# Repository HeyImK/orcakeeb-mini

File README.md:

# orcakeeb-mini

A 16-key mechanical macropad featuring a rotary encoder, per-key RGB, and a 0.91-inch OLED screen. The board is built around the Waveshare RP2040-Zero module, which handles the USB-C connection and logic, allowing for a highly compact PCB design. Fully compatible with QMK and KMK (CircuitPython) firmware.

## Pictures

| Top View | Bottom View |
| :---: | :---: |
| /topbrd.png>) | /btmbrd.png>) |

## Features

* **Main Controller:** Waveshare RP2040-Zero, providing a dual-core ARM Cortex-M0+ and natively handling USB-C and 3.3V regulation.
* **Switch Matrix:** 4x4 grid supporting 16 TTC low-profile mechanical switches, fully diode-isolated to prevent ghosting.
* **RGB Leds:** 16 reverse-mounted SK6812MINI-E LEDs sitting flush inside the switch cutouts. Powered directly via the 5V VBUS line.
* **Rotary Encoder:** Standard rotary encoder with push-button functionality. Relies on internal RP2040 pull-up resistors and software debouncing.
* **OLED Display:** I2C header for a standard 0.91" SSD1306 OLED module to display active layers, WPM, or custom graphics.

## Components Used

* **Microcontroller:** Waveshare RP2040-Zero Dev-Board
* **Switches:** 16x Cherry MX Switches or similar knock-offs
* **Diodes:** 16x 1N4148 
* **LEDs:** 16x SK6812MINI-E
* **Screen:** 0.91" SSD1306 I2C OLED Module
* **Miscellaneous:** 1x 10µF Ceramic Cap (for main 5V), 16x 0.1µF Caps (LED decoupling), EC11 (or similar knockoffs) Rotary Encoder

## Bill of Materials (BOM)

| Qty | Component | Footprint | Designator(s) |
| :---: | :--- | :--- | :--- |
| 15 | 100nf Capacitor | C_0603_1608Metric | C1, C2, C3, C5, C6, C7, C8, C9, C10, C11, C12, C13, C14, C15, C16 |
| 1 | 10uf Capacitor | C_0603_1608Metric | C17 |
| 1 | 10nF Capacitor | C_0603_1608Metric | C22 |
| 15 | SK6812MINI-E LED | LED_SK6812MINI-E_3.2x2.8mm_P1.5mm_ReverseMount | D1, D2, D3, D5, D6, D7, D8, D9, D10, D11, D12, D13, D14, D15, D16 |
| 15 | 1N4148W Diode | D_SOD-123 | D17, D18, D19, D20, D21, D22, D23, D24, D25, D26, D27, D28, D30, D31, D32 |
| 2 | 10k Resistor | R_0603_1608Metric | R3, R4 |
| 15 | SW_Push (Cherry MX) | SW_Cherry_MX_1.00u_PCB | SW1, SW2, SW3, SW4, SW5, SW6, SW7, SW8, SW9, SW10, SW11, SW12, SW14, SW15, SW16 |
| 1 | RotaryEncoder_Switch | RotaryEncoder_Alps_EC11E-Switch_Vertical_H20mm | SW19 |
| 1 | RP2040_MICRO | RP2040 MINI | U1 |
| 1 | 0.91_OLED | Untitled | U2 |

| Schematic Design |
| :---: |
| /schematics_orcakeeb.png>) |

| PCB Top Layer Routing | PCB Bottom Layer Routing |
| :---: | :---: |
| /routing_topbrd.png>) | /routing_btmbrd.png>) |

### Connections
* **VBUS (5V):** Routes power straight from the USB-C port to the main 10µF bulk capacitor, then daisy-chains to the VDD pins of all 16 LEDs. 
* **OLED Header:** Connecetd to pins (SDA) G10 (SCK) G9
* **Encoder:** Connected to Pin G4, and A And B pins to G3 and G2
* **RGB Led Data:** Data IN pins connected to G14
  
## License

This hardware project is open-source and licensed under the CERN Open Hardware Licence Version 2 - Strongly Reciprocal (CERN-OHL-S-2.0). 

You are free to copy, modify, distribute, and manufacture this board for personal or commercial use. However, if you modify these schematic or layout files and distribute your new design, you must release those modifications under this exact same CERN-OHL-S-2.0 license.

This design is shared without any warranty or implied guarantee. Check the LICENSE file for the full legal text.

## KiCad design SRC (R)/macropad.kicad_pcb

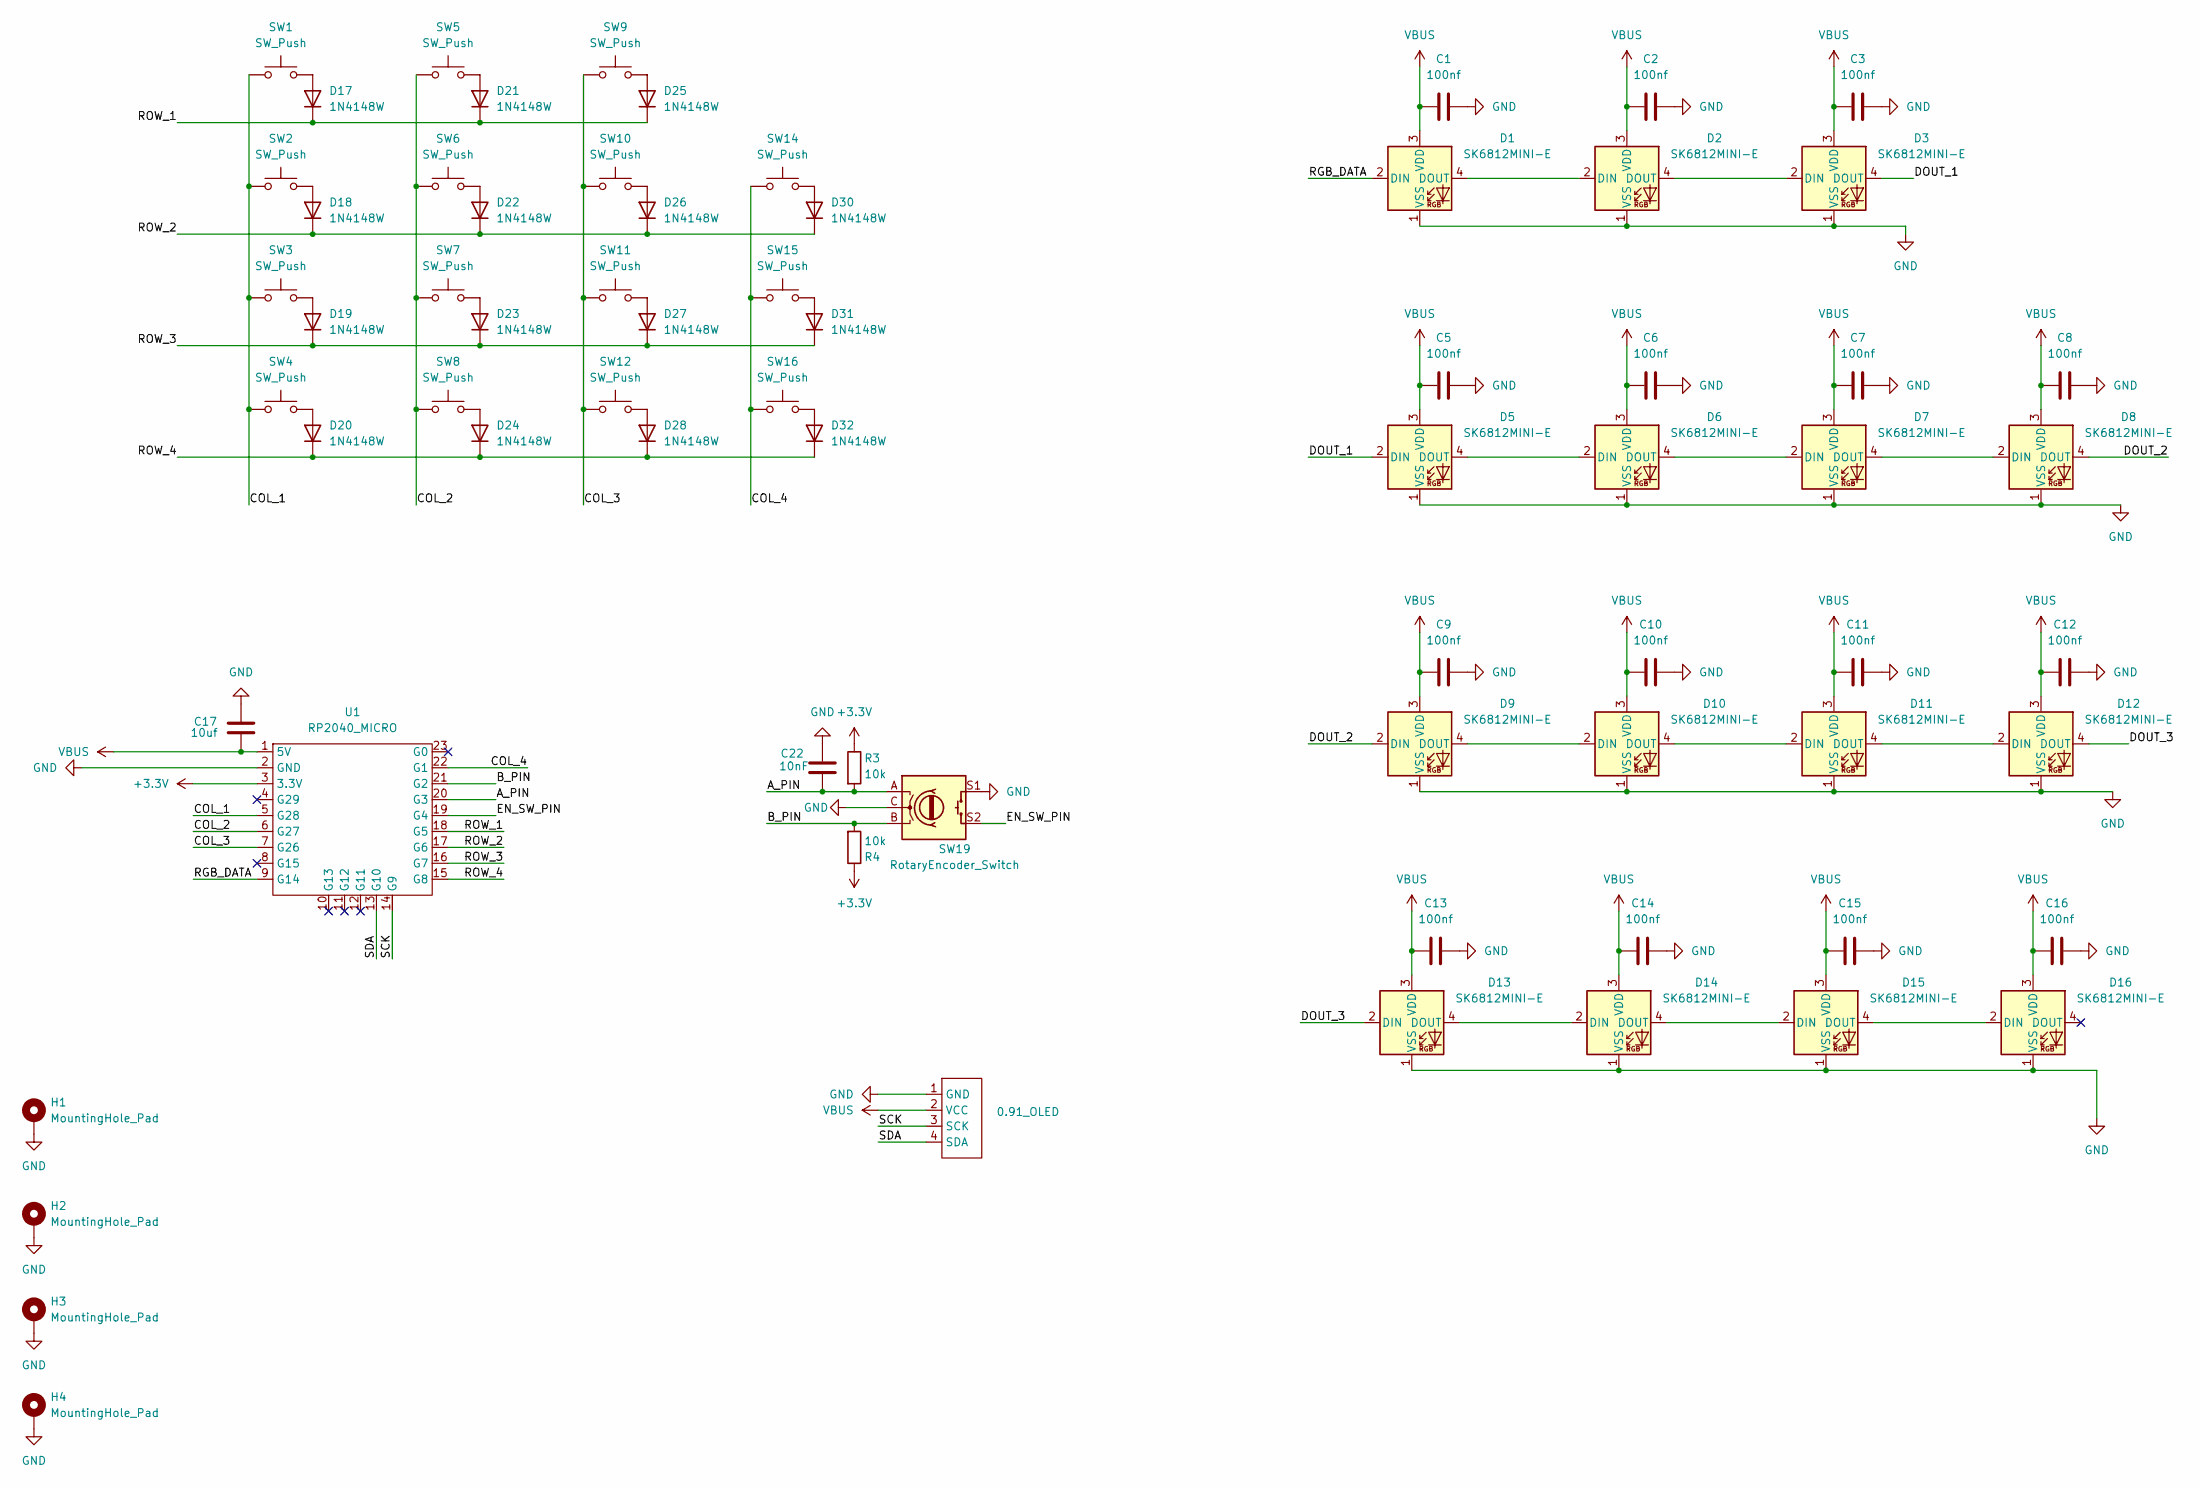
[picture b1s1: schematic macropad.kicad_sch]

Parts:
C1, C2, C3, C5, C6, C7, C8, C9, C10, C11, C12, C13, C14, C15, C16: 100nf; C_0603_1608Metric
C17: 10uf; C_0603_1608Metric
C22: 10nF; C_0603_1608Metric
D1, D2, D3, D5, D6, D7, D8, D9, D10, D11, D12, D13, D14, D15, D16: SK6812MINI-E; LED_SK6812MINI-E_3.2x2.8mm_P1.5mm_ReverseMount
D17, D18, D19, D20, D21, D22, D23, D24, D25, D26, D27, D28, D30, D31, D32: 1N4148W; D_SOD-123
H1, H2, H3, H4: MountingHole_Pad; MountingHole_2.5mm_Pad
R3, R4: 10k; R_0603_1608Metric
SW1, SW2, SW3, SW4, SW5, SW6, SW7, SW8, SW9, SW10, SW11, SW12, SW14, SW15, SW16: SW_Push; SW_Cherry_MX_1.00u_PCB
SW19: RotaryEncoder_Switch; RotaryEncoder_Alps_EC11E-Switch_Vertical_H20mm
U1: RP2040_MICRO; RP2040 MINI
U2: 0.91_OLED; Untitled

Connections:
+3.3V: R3.1, R4.1, U1.3 (3.3V)
/A_PIN: C22.1, R3.2, SW19.A, U1.20 (G3)
/B_PIN: R4.2, SW19.B, U1.21 (G2)
/COL_1: SW1.1, SW2.1, SW3.1, SW4.1, U1.5 (G28)
/COL_2: SW5.1, SW6.1, SW7.1, SW8.1, U1.6 (G27)
/COL_3: SW9.1, SW10.1, SW11.1, SW12.1, U1.7 (G26)
/COL_4: SW14.1, SW15.1, SW16.1, U1.22 (G1)
/DOUT_1: D3.4 (DOUT), D5.2 (DIN)
/DOUT_2: D8.4 (DOUT), D9.2 (DIN)
/DOUT_3: D12.4 (DOUT), D13.2 (DIN)
/EN_SW_PIN: SW19.S2, U1.19 (G4)
/RGB_DATA: D1.2 (DIN), U1.9 (G14)
/ROW_1: D17.1 (K), D21.1 (K), D25.1 (K), U1.18 (G5)
/ROW_2: D18.1 (K), D22.1 (K), D26.1 (K), D30.1 (K), U1.17 (G6)
/ROW_3: D19.1 (K), D23.1 (K), D27.1 (K), D31.1 (K), U1.16 (G7)
/ROW_4: D20.1 (K), D24.1 (K), D28.1 (K), D32.1 (K), U1.15 (G8)
/SCK: U1.14 (G9), U2.3 (SCK)
/SDA: U1.13 (G10), U2.4 (SDA)
GND: C1.2, C2.2, C3.2, C5.2, C6.2, C7.2, C8.2, C9.2, C10.2, C11.2, C12.2, C13.2, C14.2, C15.2, C16.2, C17.1, C22.2, D1.1 (VSS), D2.1 (VSS), D3.1 (VSS), D5.1 (VSS), D6.1 (VSS), D7.1 (VSS), D8.1 (VSS), D9.1 (VSS), D10.1 (VSS), D11.1 (VSS), D12.1 (VSS), D13.1 (VSS), D14.1 (VSS), D15.1 (VSS), D16.1 (VSS), H1.1 (1_1), H2.1 (1_1), H3.1 (1_1), H4.1 (1_1), SW19.C, SW19.S1, U1.2 (GND), U2.1 (GND)
unnamed: D1.4 (DOUT), D2.2 (DIN)
unnamed: D2.4 (DOUT), D3.2 (DIN)
unnamed: D5.4 (DOUT), D6.2 (DIN)
unnamed: D6.4 (DOUT), D7.2 (DIN)
unnamed: D7.4 (DOUT), D8.2 (DIN)
unnamed: D9.4 (DOUT), D10.2 (DIN)
unnamed: D10.4 (DOUT), D11.2 (DIN)
unnamed: D11.4 (DOUT), D12.2 (DIN)
unnamed: D13.4 (DOUT), D14.2 (DIN)
unnamed: D14.4 (DOUT), D15.2 (DIN)
unnamed: D15.4 (DOUT), D16.2 (DIN)
unnamed: D17.2 (A), SW1.2
unnamed: D18.2 (A), SW2.2
unnamed: D19.2 (A), SW3.2
unnamed: D20.2 (A), SW4.2
unnamed: D21.2 (A), SW5.2
unnamed: D22.2 (A), SW6.2
unnamed: D23.2 (A), SW7.2
unnamed: D24.2 (A), SW8.2
unnamed: D25.2 (A), SW9.2
unnamed: D26.2 (A), SW10.2
unnamed: D27.2 (A), SW11.2
unnamed: D28.2 (A), SW12.2
unnamed: D30.2 (A), SW14.2
unnamed: D31.2 (A), SW15.2
unnamed: D32.2 (A), SW16.2
VBUS: C1.1, C2.1, C3.1, C5.1, C6.1, C7.1, C8.1, C9.1, C10.1, C11.1, C12.1, C13.1, C14.1, C15.1, C16.1, C17.2, D1.3 (VDD), D2.3 (VDD), D3.3 (VDD), D5.3 (VDD), D6.3 (VDD), D7.3 (VDD), D8.3 (VDD), D9.3 (VDD), D10.3 (VDD), D11.3 (VDD), D12.3 (VDD), D13.3 (VDD), D14.3 (VDD), D15.3 (VDD), D16.3 (VDD), U1.1 (5V), U2.2 (VCC)

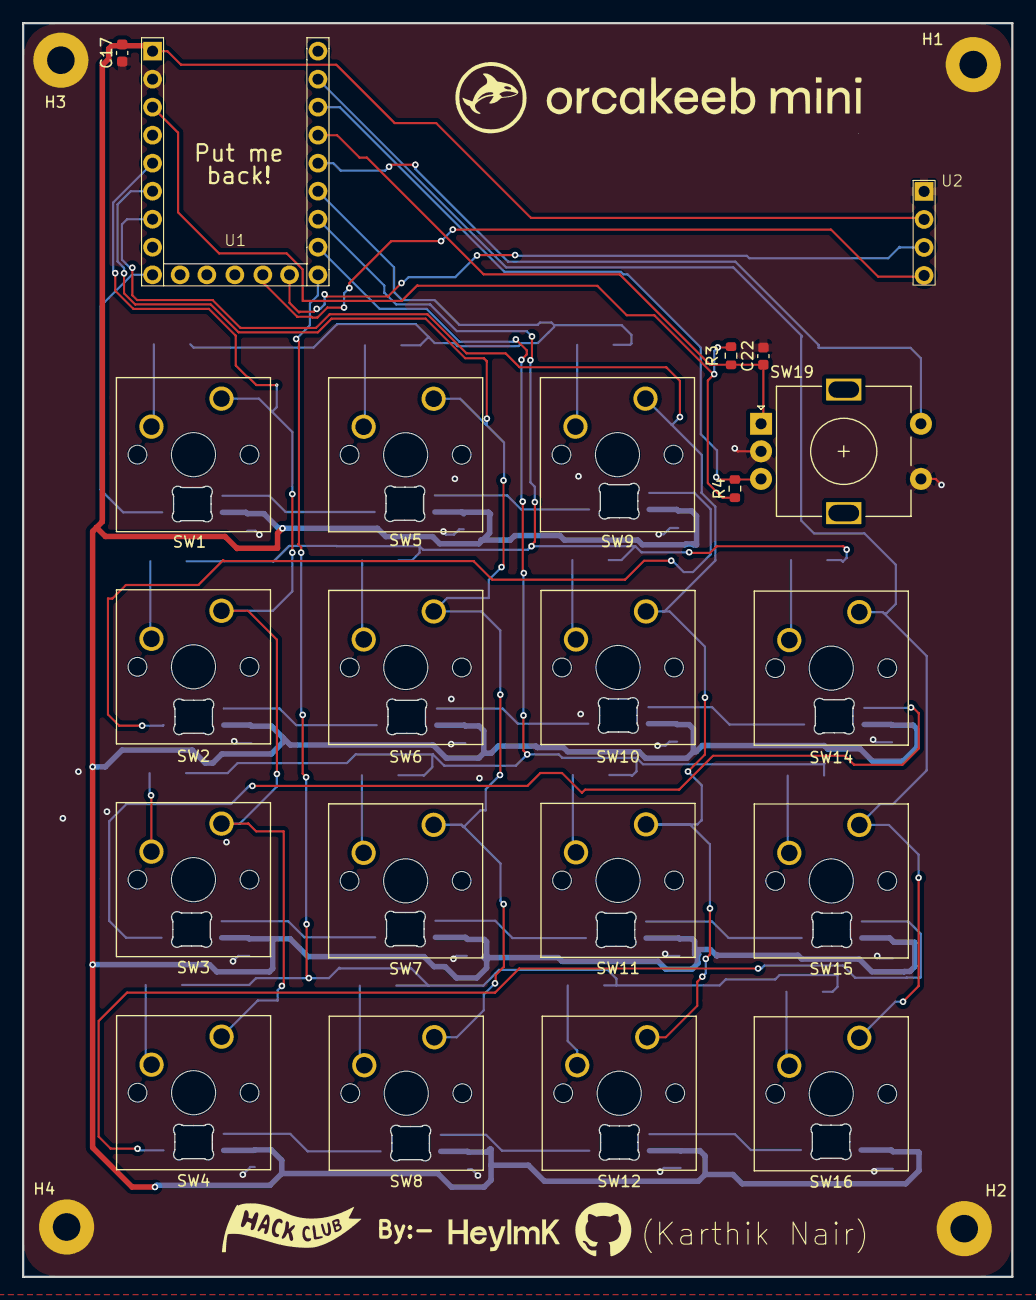
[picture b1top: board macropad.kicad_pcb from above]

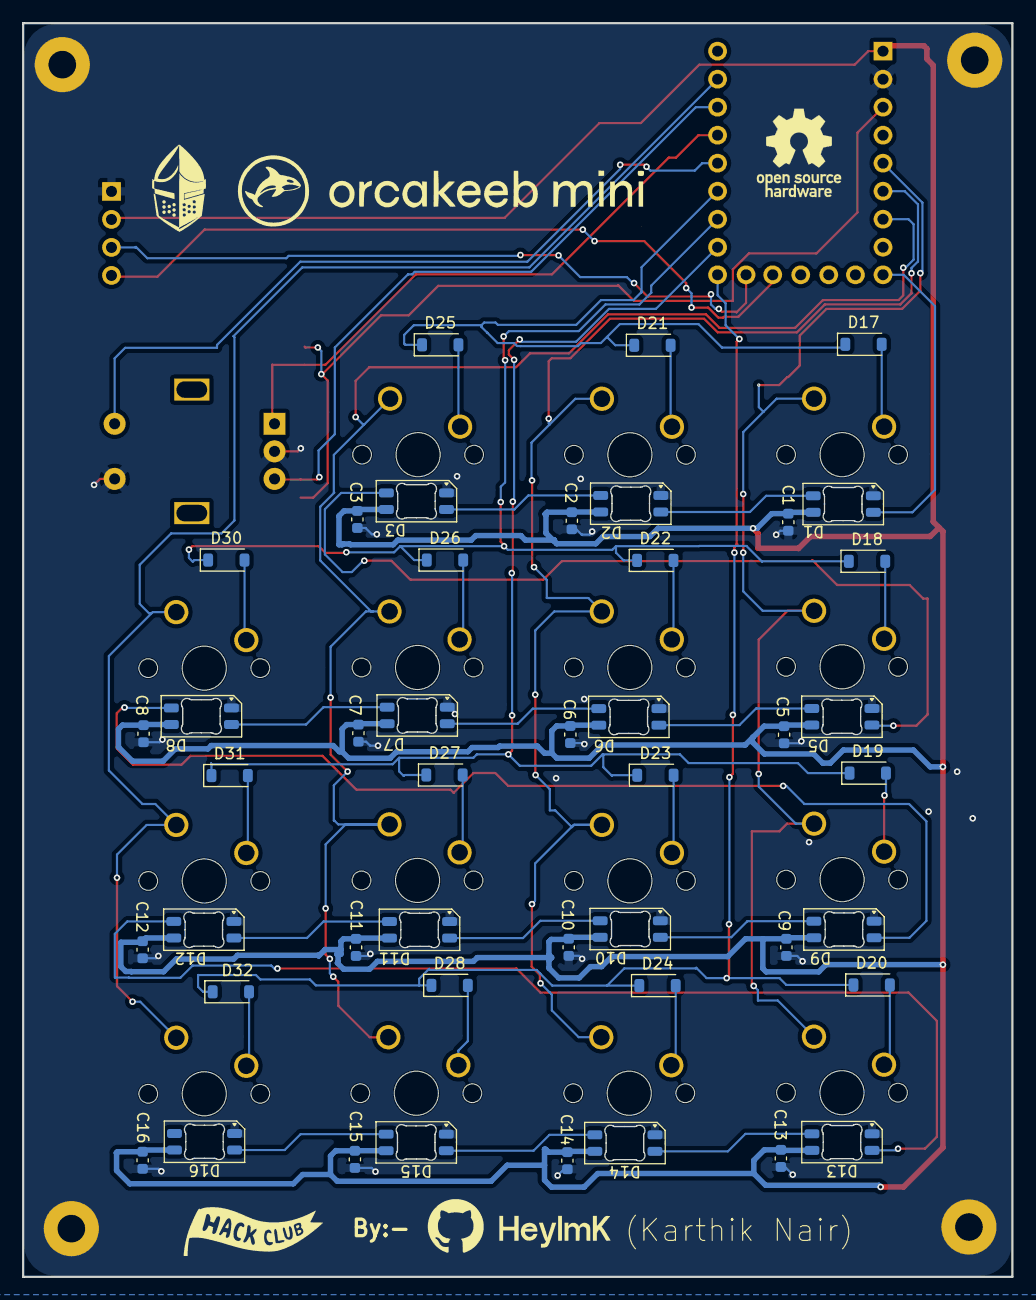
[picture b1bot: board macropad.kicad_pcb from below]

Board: 2 copper layers, 89.7 x 113.7 mm, 71 parts (45 on the bottom side), 46 nets.
